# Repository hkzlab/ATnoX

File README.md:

# ATnoX

## Introduction

The ATnoX was born out of the necessity for me to have a small adapter adapter I could use to fit AT/XT motherboards into modern cases, powering them with ATX power supplies and turning them on with a momentary switch (the standard power on button present in computer cases built in the last 20+ years).

The [ATX2AT](https://x86.fr/atx2at-smart-converter/) is a wonderful device (I own several of them), but I prefer to use it to test my boards and then fall back onto a cheaper alternative I can close inside a case without it feeling like a waste.

In fact, the output connector uses the same pinout as the ATX2AT, but as I still had a free pin available, I decided to include a **TICK generator**: a 50/60hz square wave signal required by some big-box Amigas to turn on.

## Pinout

14 pin connector, front view.

```text
                ____
.----.----.----|----|----.----.----.
| 14 | 13 | 12 | 11 | 10 |  9 |  8 |
|----+----+----+----+----+----+----|
|  7 |  6 |  5 |  4 |  3 |  2 |  1 |
'----'----'----'----'----'----'----'
```

1. +12V
2. +5V
3. +5V
4. GND
5. GND
6. TICK (50/60Hz depending on X1)
7. -5V
8. +12V
9. +5V
10. +5V
11. GND
12. GND
13. Power OK signal
14. -12V

## Component list

**TODO**

## Features

- -5v onboard generation via a 7905 regulator
- Momentary button power-on support
- Header for power led in case the motherboard lacks it
- Power on button included on board for bench testing
- Optional amiga Tick generator
- 4 Layer board (middle layers are +5v and GND)

## Credits

- logic-4000 libraries taken from [alexisvl/kicad-schlib](https://github.com/alexisvl/kicad-schlib)
- ATX power-on circuit taken from [skiselev/isa8_backplane](https://github.com/skiselev/isa8_backplane)
- Amiga Tick generator taken from [Aminet](http://aminet.net/package/docs/hard/Mix_and_Tick)
- Thanks to [@A-Small-Mice](https://github.com/A-Small-Mice) for the printable case

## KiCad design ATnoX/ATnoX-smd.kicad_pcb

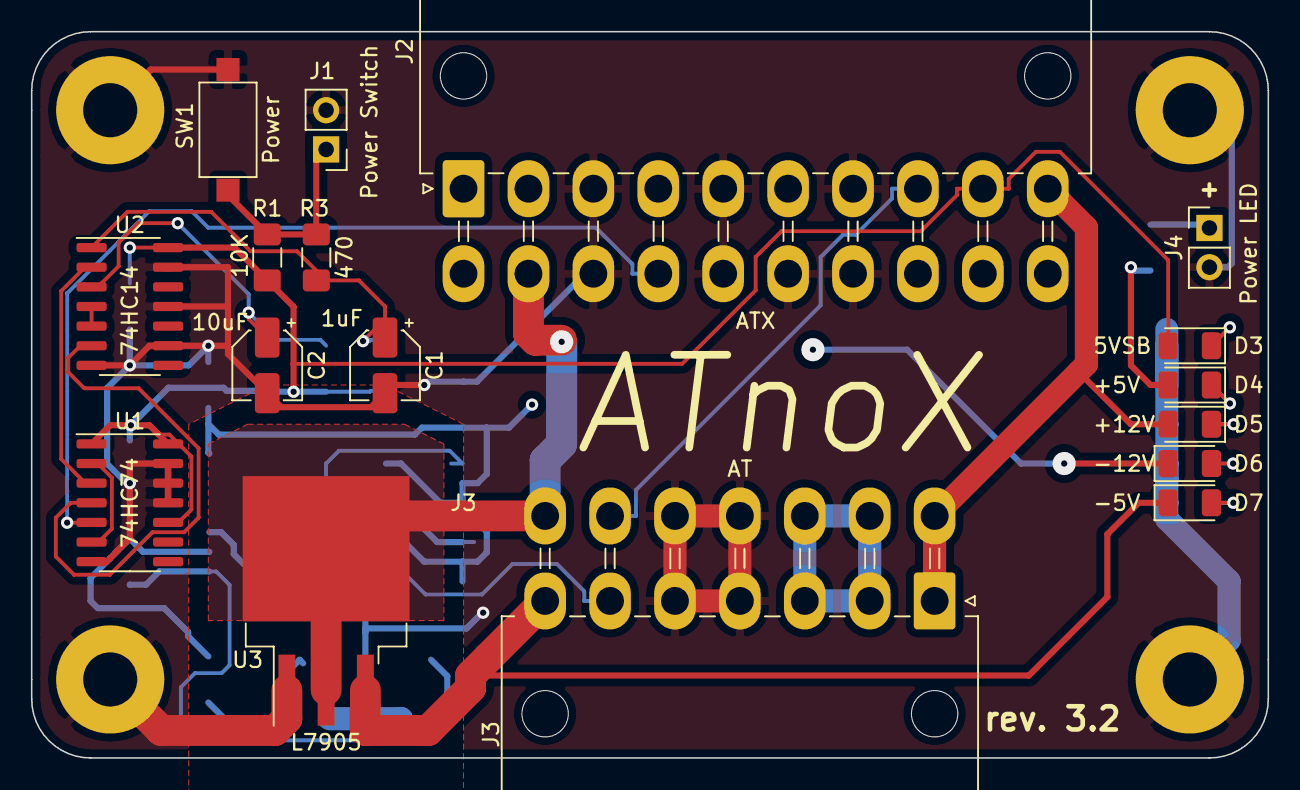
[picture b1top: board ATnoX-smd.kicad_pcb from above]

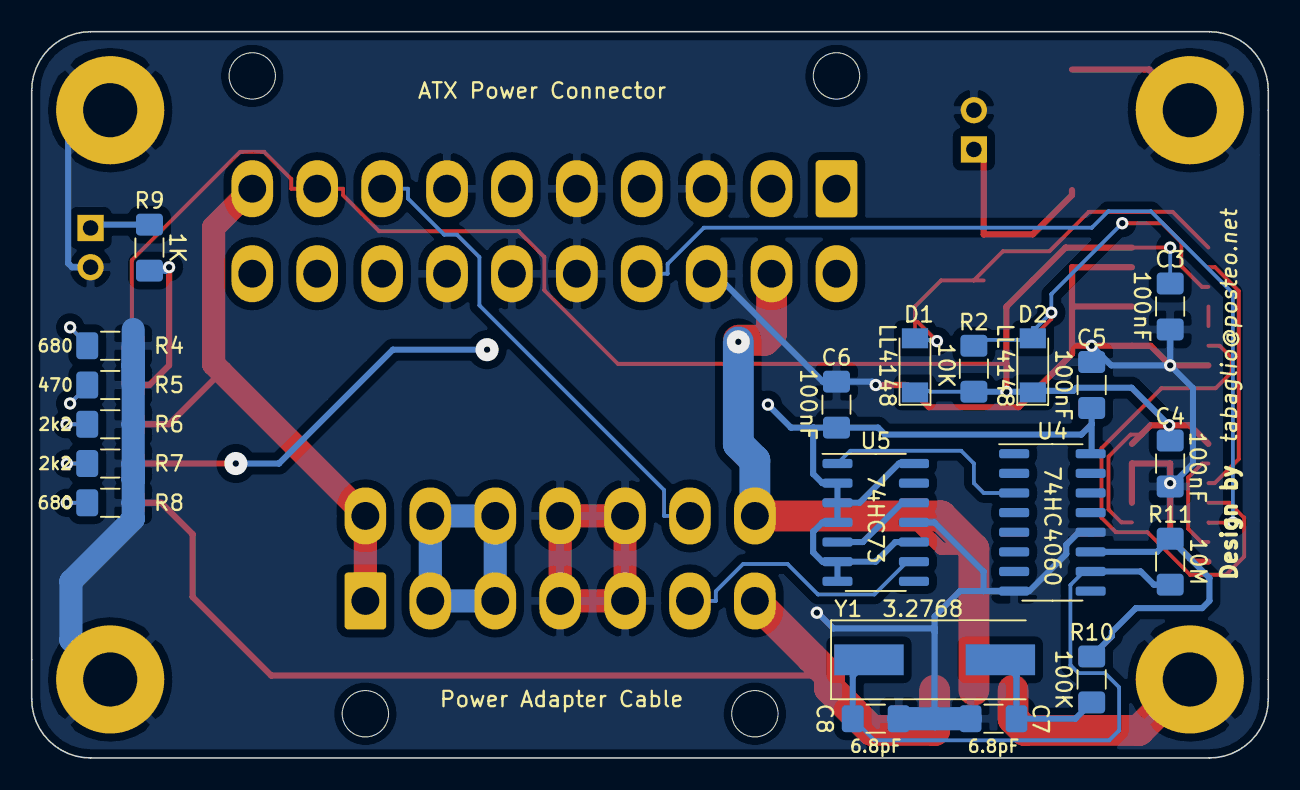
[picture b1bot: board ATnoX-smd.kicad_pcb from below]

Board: 4 copper layers, 80.0 x 47.0 mm, 41 parts (20 on the bottom side), 27 nets.

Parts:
C1: 1uF; CP_Elec_4x5.3
C2: 10uF; CP_Elec_4x5.3
C3, C4, C5, C6: 100nF; C_1206_3216Metric_Pad1.42x1.75mm_HandSolder
C7, C8: 6.8pF; C_1206_3216Metric_Pad1.42x1.75mm_HandSolder
D1, D2: LL4148; D_MiniMELF
D3: 5VSB; LED_1206_3216Metric
D4: +5V; LED_1206_3216Metric
D5: +12V; LED_1206_3216Metric
D6: -12V; LED_1206_3216Metric
D7: -5V; LED_1206_3216Metric
H1, H2, H3, H4: MountingHole_Pad; MountingHole_3.5mm_Pad
J1: Power Switch; PinHeader_1x02_P2.54mm_Vertical
J2: ATX; Molex_Mini-Fit_Jr_5569-20A2_2x10_P4.20mm_Horizontal
J3: AT; Molex_Mini-Fit_Jr_5569-14A2_2x07_P4.20mm_Horizontal
J4: Power LED; PinHeader_1x02_P2.54mm_Vertical
R1, R2: 10K; R_1206_3216Metric_Pad1.42x1.75mm_HandSolder
R3, R5: 470; R_1206_3216Metric_Pad1.42x1.75mm_HandSolder
R4, R8: 680; R_1206_3216Metric_Pad1.42x1.75mm_HandSolder
R6, R7: 2k2; R_1206_3216Metric_Pad1.42x1.75mm_HandSolder
R9: 1K; R_1206_3216Metric_Pad1.42x1.75mm_HandSolder
R10: 100K; R_1206_3216Metric_Pad1.42x1.75mm_HandSolder
R11: 10M; R_1206_3216Metric_Pad1.42x1.75mm_HandSolder
SW1: Power; SW_SPST_CK_RS282G05A3
U1: 74HC74; SOIC-14_3.9x8.7mm_P1.27mm
U2: 74HC14; SOIC-14_3.9x8.7mm_P1.27mm
U3: L7905; TO-263-3_TabPin2
U4: 74HC4060; SOIC-16_3.9x9.9mm_P1.27mm
U5: 74HC73; SOIC-14_3.9x8.7mm_P1.27mm
Y1: 3.2768; Crystal_SMD_HC49-SD

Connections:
/5VSB: C3.1, C4.1, D1.1, D2.1, D3.2, J2.9, R1.1, R2.1, U1.1, U1.10, U1.14, U2.14
/+12V: D5.2, J2.10, J3.1, J3.8
/-5V: D7.1, J3.7, U3.3
/-12V: D6.1, J2.12, J3.14, U3.2
/PWR_OK: J2.8, J3.13
/PWR_SW: J1.1, R1.2, R3.2, SW1.2
/TICK: J3.6, U5.9
/~PS_ON: J2.14, U1.5
GND: C1.2, C2.2, C3.2, C4.2, C5.1, C6.1, C7.2, C8.2, H1.1, H2.1, H3.1, H4.1, J1.2, J2.3, J2.5, J2.7, J2.13, J2.15, J2.16, J2.17, J3.4, J3.5, J3.11, J3.12, J4.2, R4.1, R5.1, R6.1, R7.1, R8.1, SW1.1, U1.7, U1.11, U1.12, U1.13, U2.7, U2.9, U2.11, U2.13, U3.1, U4.8, U4.12, U5.11
unnamed: C1.1, D1.2, R3.1, U2.1
unnamed: C2.1, D2.2, R2.2, U2.3
unnamed: C7.1, R10.2, Y1.2
unnamed: C8.1, R11.1, U4.10, Y1.1
unnamed: D3.1, R4.2
unnamed: D4.1, R5.2
unnamed: D5.1, R6.2
unnamed: D6.2, R7.2
unnamed: D7.2, R8.2
unnamed: J4.1, R9.2
unnamed: R10.1, R11.2, U4.11
unnamed: U1.2, U1.6
unnamed: U1.3, U2.2
unnamed: U1.4, U2.6
unnamed: U2.4, U2.5
unnamed: U4.3, U5.1
unnamed: U5.5, U5.12
VCC: C5.2, C6.2, D4.2, J2.4, J2.6, J2.19, J2.20, J3.2, J3.3, J3.9, J3.10, R9.1, U4.16, U5.2, U5.3, U5.4, U5.6, U5.7, U5.10, U5.14

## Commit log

2019-11-22 Add Kicad project
2019-11-22 More of the circuit done
2019-11-23 Update schematic
2019-11-23 Add power leds
2019-11-23 First draft of the schematic
2019-11-23 Fix error
2019-11-24 Add some footprints
2019-11-24 Add footprintd
2019-11-24 Change footprints
2019-11-24 Update PCB schematic
2019-11-24 Add filter caps
2019-11-24 Some more work
2019-11-26 Design PCB
2019-11-26 Some Tweaks
2019-11-26 Tweaks
2019-11-28 Update PCB
2020-01-25 Add gerbers
2020-02-04 Add SMD variant
2020-02-04 Fix design, update gerbers
2020-02-05 Add ATLessX smd gerbers
2020-02-05 Better ATnoX PCB
2020-02-05 Add 2 layer version
2020-02-05 Added better continuity between 5VSB and GND top/bottom
2020-02-05 Update gerbers
2020-02-06 Add new revision of board
2020-02-06 Add rev2 board
2020-08-02 Turned the SMD version into a 4layer board
2020-09-01 Add rev. 2.5 of SMD variant
2020-09-01 Rev 3
2020-09-01 Clear a DRC issue
2020-09-01 Remove tracks ending in a no routing zone
2020-09-01 Add thermal relief pads
2020-09-01 Add gerbers for rev.3
2020-09-01 Update r3 gerbers
2020-09-01 Add silkscreen text
2020-09-02 Removed old versions, fix wrong pin connected to 4, rev 3.1
2020-09-02 Fix paths and update gerbers
2020-09-02 Cleanup
2020-10-09 Begin adding some documentation to the project
2020-10-09 Add LICENSE
2021-06-02 Forgot to commit sym table
2021-06-02 Add r3.2 gerbers
2021-06-02 Updated for rev 3.2
2021-06-02 slight adjustment to silkscreen
2021-11-09 Changed kicad url
2023-12-03 Add a 3D model for ATnoX
2023-12-09 Add credits for printable case
